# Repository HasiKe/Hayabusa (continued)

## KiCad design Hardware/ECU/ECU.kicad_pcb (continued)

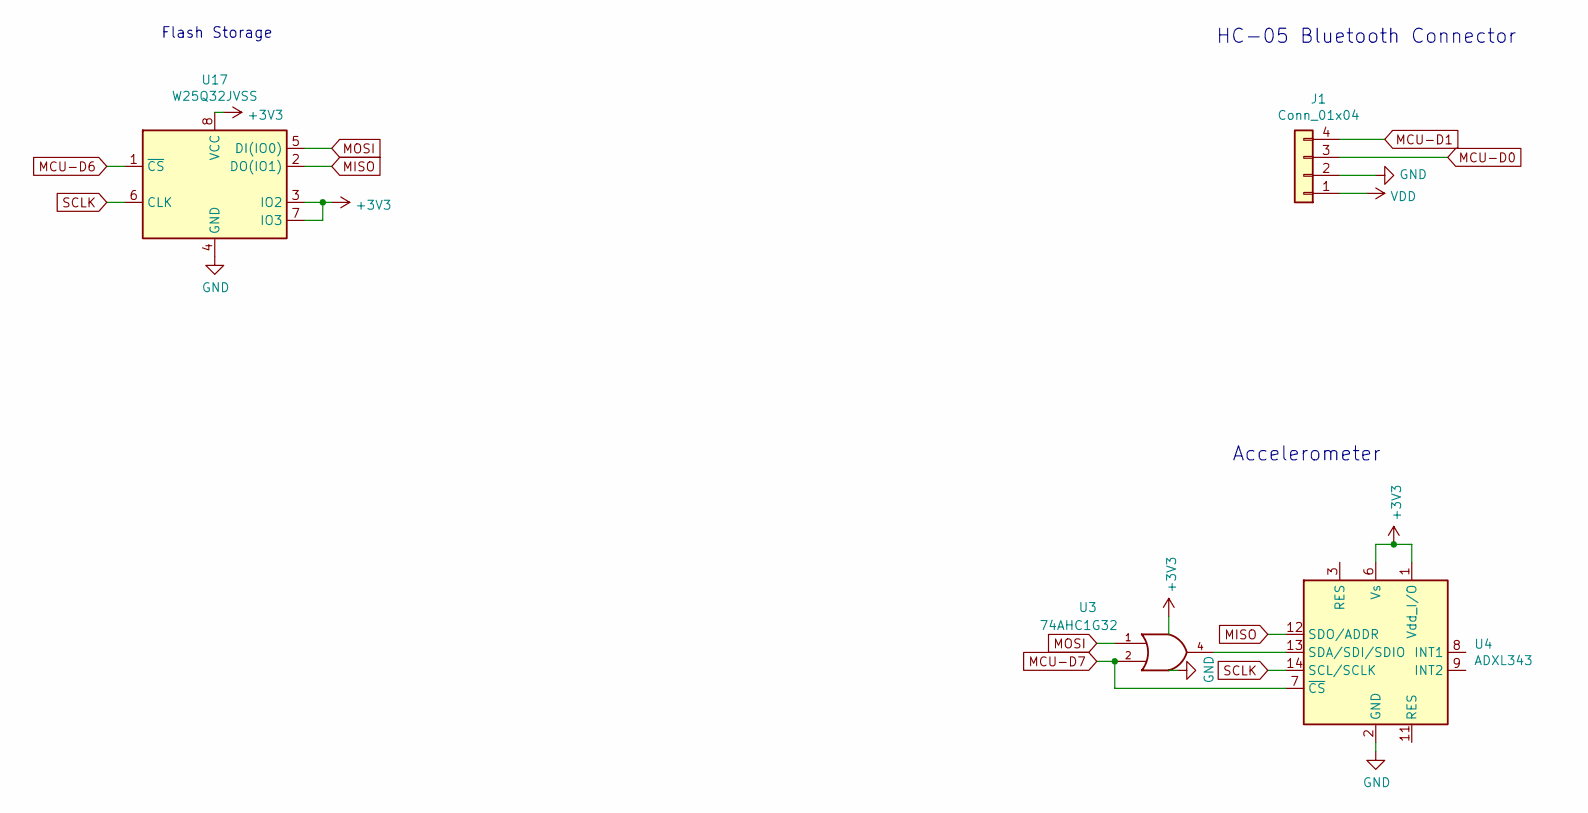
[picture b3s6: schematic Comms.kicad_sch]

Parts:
J1: Conn_01x04; PinHeader_1x04_P2.54mm_Vertical
U3: 74AHC1G32; SOT-353_SC-70-5; Manufacturer_Part_Number SN74AHC1G32DCKR; Digikey Part Number 296-8749-1-ND
U4: ADXL343; LGA-14_3x5mm_P0.8mm_LayoutBorder1x6y; Manufacturer_Part_Number ADXL343BCCZ-RL; Digikey Part Number ADXL343BCCZ-RLCT-ND
U17: W25Q32JVSS; SOIC-8_5.3x5.3mm_P1.27mm; Manufacturer_Part_Number W25Q32JVSSIQ; Digikey Part Number W25Q32JVSSIQCT-ND

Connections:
+3V3: U3.5 (VCC), U4.1 (Vdd_I/O), U4.6 (Vs), U17.3 (IO2), U17.7 (IO3), U17.8 (VCC); also elsewhere on the board
+5V: J1.1; also elsewhere on the board
GND: J1.2, U3.3 (GND), U4.2 (GND), U4.4 (GND), U4.5 (GND), U17.4 (GND); also elsewhere on the board
MCU-D0: J1.3; also elsewhere on the board
MCU-D1: J1.4; also elsewhere on the board
MCU-D6: U17.1 (~CS); also elsewhere on the board
MCU-D7: U3.2, U4.7 (~CS); also elsewhere on the board
MISO: U4.12 (SDO/ADDR), U17.2 (DO(IO1)); also elsewhere on the board
MOSI: U3.1, U17.5 (DI(IO0)); also elsewhere on the board
unnamed: U3.4, U4.13 (SDA/SDI/SDIO)
SCLK: U4.14 (SCL/SCLK), U17.6 (CLK); also elsewhere on the board

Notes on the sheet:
Flash Storage
HC-05 Bluetooth Connector
Accelerometer

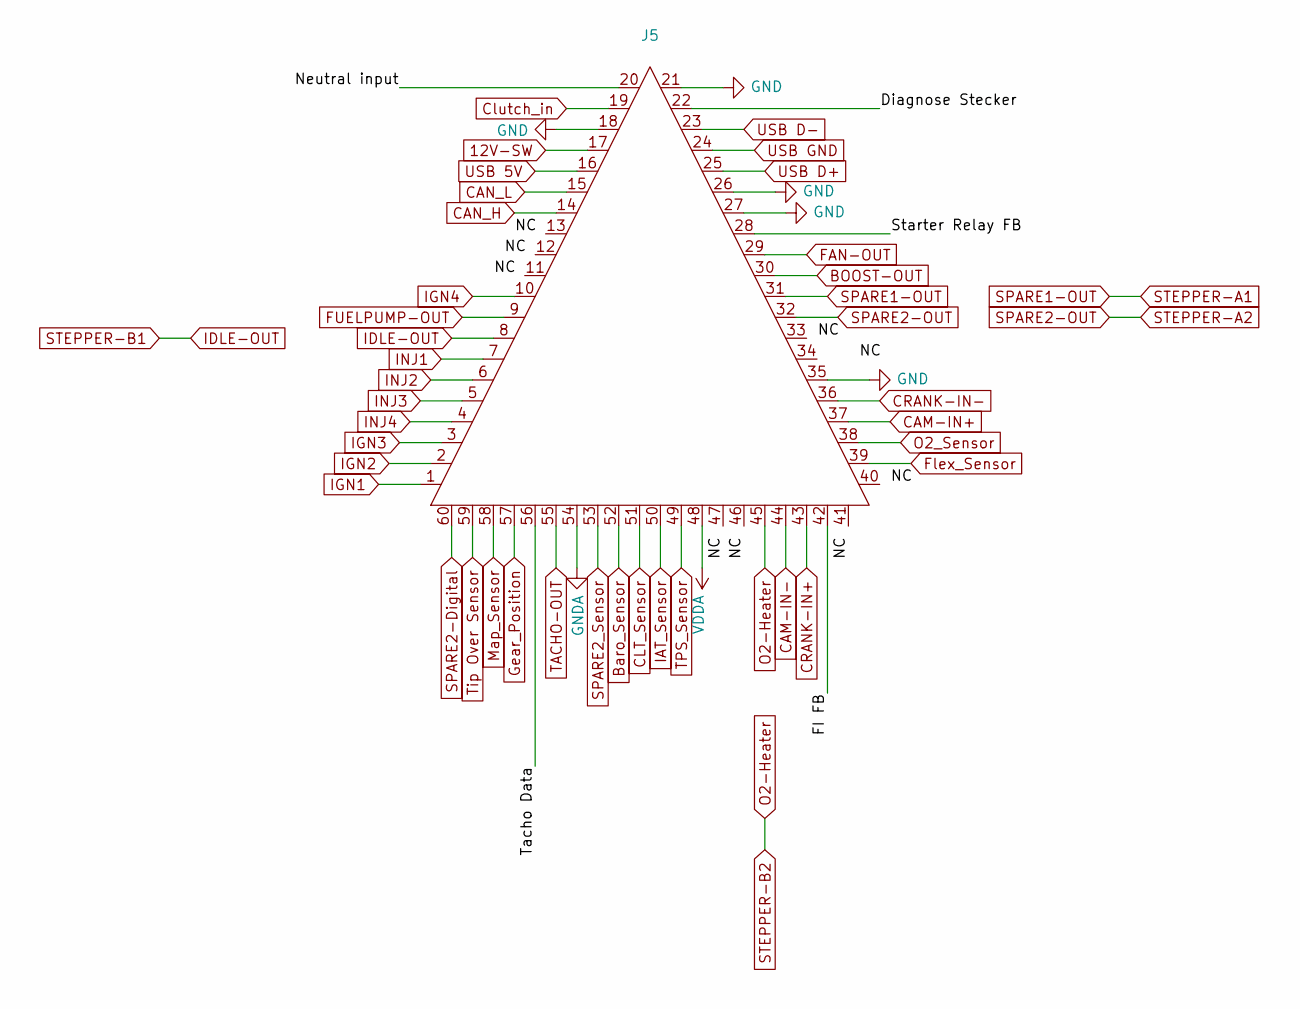
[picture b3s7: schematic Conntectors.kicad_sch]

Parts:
J5: 6437288-3

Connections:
12V-SW: J5.17; also elsewhere on the board
/Conntectors/Diagnose Stecker: J5.22
/Conntectors/FI FB: J5.42
/Conntectors/Neutral input: J5.20
/Conntectors/Starter Relay FB: J5.28
/Conntectors/Tacho Data: J5.56
ADC-Clamp-5: J5.39; also elsewhere on the board
BOOST-OUT: J5.30; also elsewhere on the board
Baro_Sensor: J5.52; also elsewhere on the board
CAM-IN+: J5.37; also elsewhere on the board
CAM-IN-: J5.44; also elsewhere on the board
CAN_H: J5.14
CAN_L: J5.15
CLT_Sensor: J5.51; also elsewhere on the board
CRANK-IN+: J5.43; also elsewhere on the board
CRANK-IN-: J5.36; also elsewhere on the board
Clutch_in: J5.19; also elsewhere on the board
FAN-OUT: J5.29; also elsewhere on the board
GND: J5.18, J5.21, J5.26, J5.27, J5.35; also elsewhere on the board
GNDA: J5.54; also elsewhere on the board
Gear_Position: J5.57; also elsewhere on the board
IAT_Sensor: J5.50; also elsewhere on the board
IDLE-OUT: J5.8; also elsewhere on the board
IGN1: J5.1; also elsewhere on the board
IGN2: J5.2; also elsewhere on the board
IGN3: J5.3; also elsewhere on the board
IGN4: J5.10; also elsewhere on the board
INJ1: J5.7; also elsewhere on the board
INJ2: J5.6; also elsewhere on the board
INJ3: J5.5; also elsewhere on the board
INJ4: J5.4; also elsewhere on the board
Map_Sensor: J5.58; also elsewhere on the board
O2-Heater: J5.45; also elsewhere on the board
O2_Sensor: J5.38; also elsewhere on the board
ROUT2: J5.55; also elsewhere on the board
SPARE1-OUT: J5.31; also elsewhere on the board
SPARE2-Digital: J5.60; also elsewhere on the board
SPARE2-OUT: J5.32; also elsewhere on the board
SPARE2_Sensor: J5.53; also elsewhere on the board
TPS_Sensor: J5.49; also elsewhere on the board
Tip Over Sensor: J5.59; also elsewhere on the board
USB 5V: J5.16; also elsewhere on the board
USB D+: J5.25; also elsewhere on the board
USB D-: J5.23; also elsewhere on the board
USB GND: J5.24; also elsewhere on the board
VDDA: J5.48; also elsewhere on the board

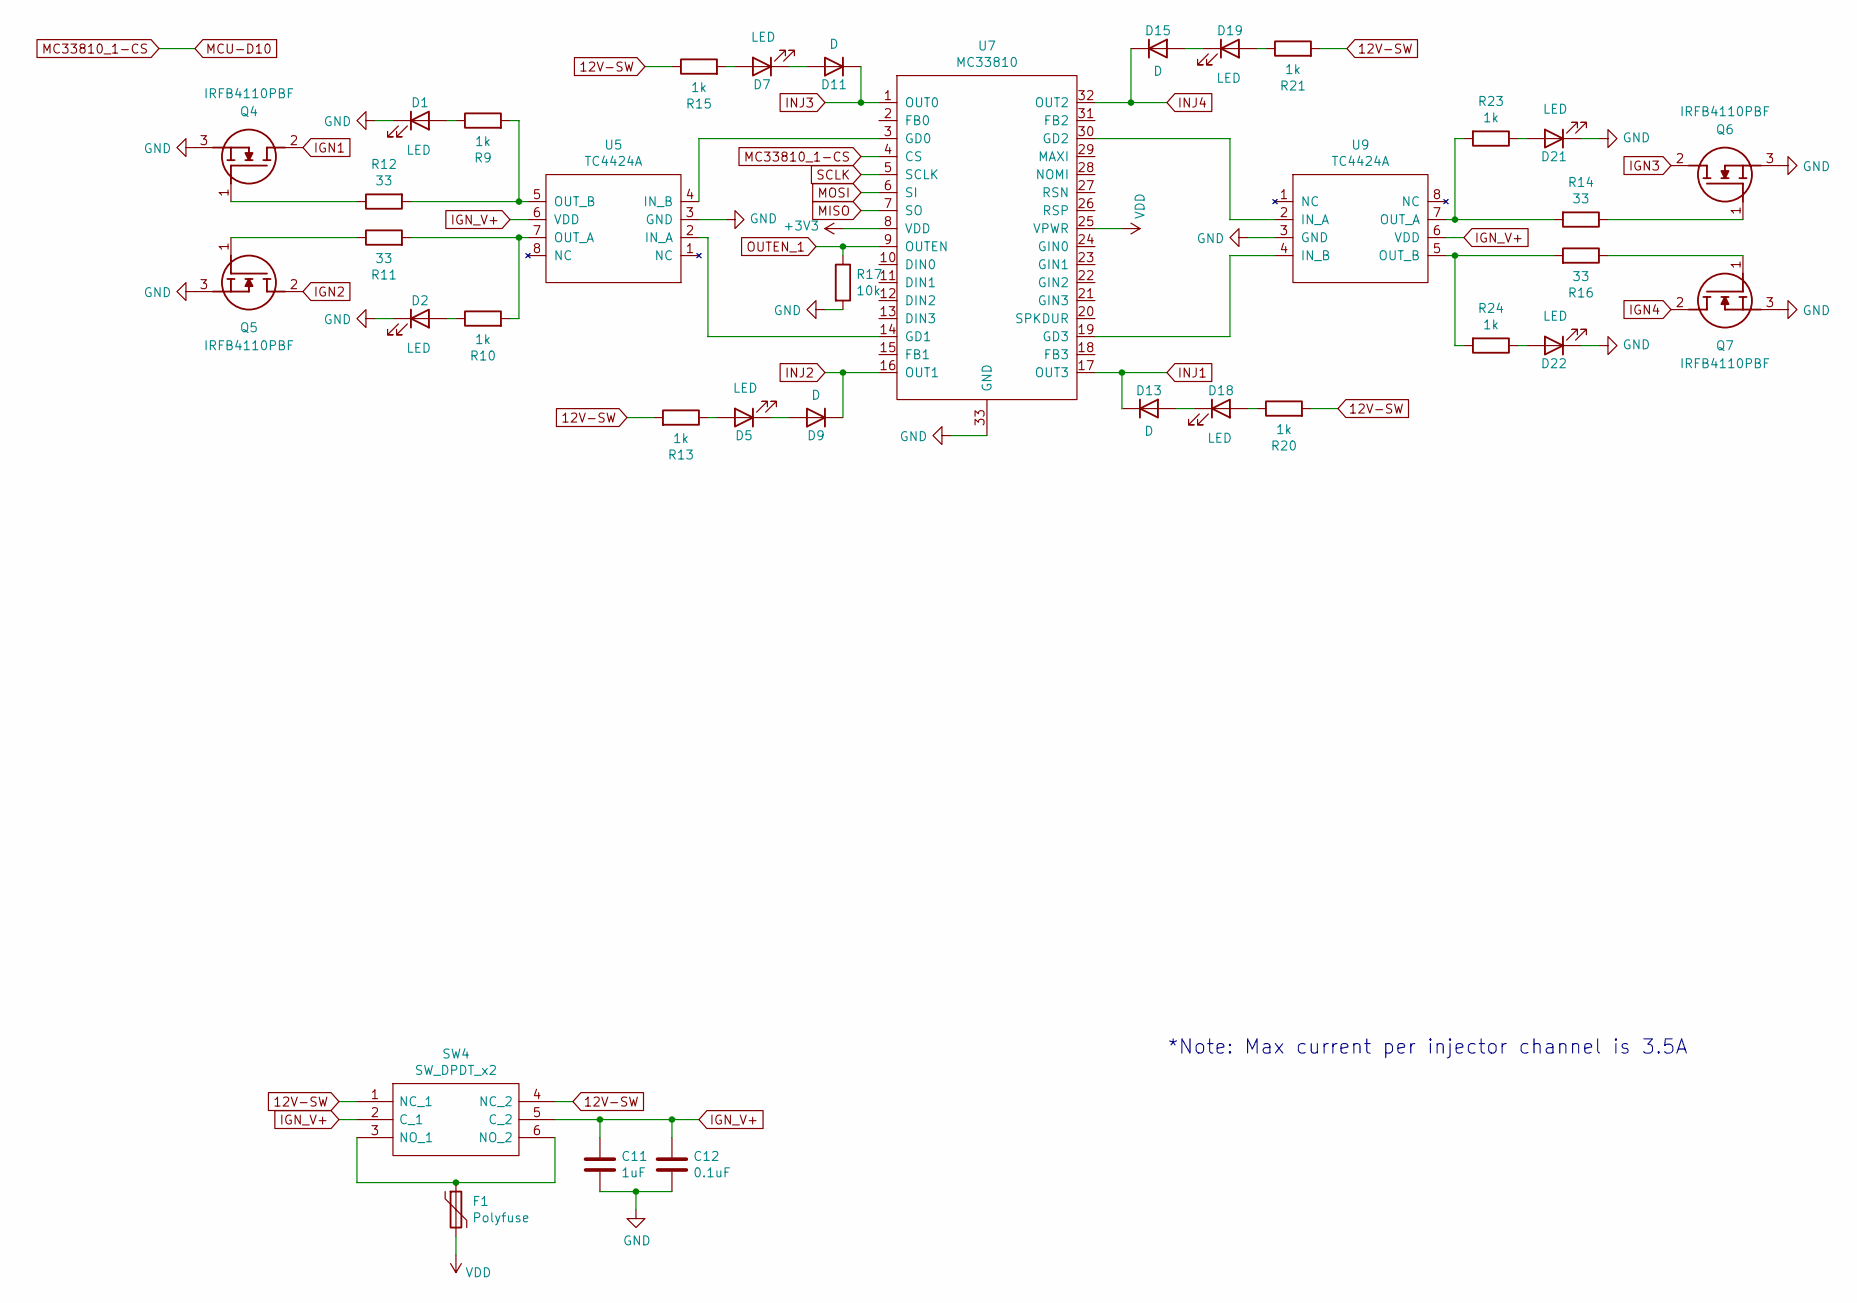
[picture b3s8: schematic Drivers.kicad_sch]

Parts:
C11: 1uF; C_0805_2012Metric; Manufacturer_Part_Number CC0805KKX7R7BB105; Digikey Part Number 311-1365-1-ND
C12: 0.1uF; C_0805_2012Metric; Manufacturer_Part_Number CC0805KRX7R9BB104; Digikey Part Number 311-1140-1-ND
D1, D2, D21, D22: LED; LED_0805_2012Metric; Manufacturer_Part_Number SML-H12D8TT86C; Digikey Part Number SML-H12D8TT86CCT-ND
D5, D7, D18, D19: LED; LED_0805_2012Metric; Manufacturer_Part_Number LH R974-LP-1; Digikey Part Number 475-1415-1-ND
D9, D11, D13, D15: D; D_SOD-323; Manufacturer_Part_Number 1N4448WX-TP; Digikey Part Number 1N4448WXTPMSCT-ND
F1: Polyfuse; Fuse_1812_4532Metric; Manufacturer_Part_Number 0ZCC0050FF2C; Digikey Part Number 507-1361-1-ND
Q4, Q5, Q6, Q7: IRFB4110PBF; TO254P483X1016X1994-3P; Mouser Part Number 942-IRFB4110PBF
R9, R10, R13, R15, R20, R21, R23, R24: 1k; R_0805_2012Metric; Manufacturer_Part_Number RC0805FR-071KL; Digikey Part Number 311-1.00KCRCT-ND
R11, R12, R14, R16: 33; R_0805_2012Metric; Manufacturer_Part_Number RC0805FR-7W33RL; Digikey Part Number RC0805FR-7W33RL
R17: 10k; R_0805_2012Metric; Manufacturer_Part_Number RC0805JR-0710KL; Digikey Part Number 311-10KARCT-ND
SW4: SW_DPDT_x2; AYZ0202AGRLC; Manufacturer_Part_Number AYZ0202AGRLC; Digikey Part Number 401-2013-1-ND
U5, U9: TC4424A; SOIC-8_3.9x4.9mm_P1.27mm; Manufacturer_Part_Number TC4424AVOA; Digikey Part Number TC4424AVOA-ND
U7: MC33810; SOIC32-P0.65-33N; Manufacturer_Part_Number MCZ33810EK

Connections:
12V-SW: R13.2, R15.1, R20.2, R21.2, SW4.1 (NC_1), SW4.4 (NC_2); also elsewhere on the board
+3V3: U7.8 (VDD); also elsewhere on the board
+5V: F1.2, U7.25 (VPWR); also elsewhere on the board
GND: C11.2, C12.2, D1.1 (K), D2.1 (K), D21.1 (K), D22.1 (K), Q4.3 (S), Q5.3 (S), Q6.3 (S), Q7.3 (S), R17.2, U5.3 (GND), U7.33 (GND), U9.3 (GND); also elsewhere on the board
IGN1: Q4.2 (D); also elsewhere on the board
IGN2: Q5.2 (D); also elsewhere on the board
IGN3: Q6.2 (D); also elsewhere on the board
IGN4: Q7.2 (D); also elsewhere on the board
IGN_V+: C11.1, C12.1, SW4.2 (C_1), SW4.5 (C_2), U5.6 (VDD), U9.6 (VDD)
INJ1: D13.1 (K), U7.17 (OUT3); also elsewhere on the board
INJ2: D9.1 (K), U7.16 (OUT1); also elsewhere on the board
INJ3: D11.1 (K), U7.1 (OUT0); also elsewhere on the board
INJ4: D15.1 (K), U7.32 (OUT2); also elsewhere on the board
MC33810_1-CS: U7.4 (CS); also elsewhere on the board
MISO: U7.7 (SO); also elsewhere on the board
MOSI: U7.6 (SI); also elsewhere on the board
unnamed: D1.2 (A), R9.1
unnamed: D2.2 (A), R10.1
unnamed: D5.2 (A), R13.1
unnamed: D5.1 (K), D9.2 (A)
unnamed: D7.2 (A), R15.2
unnamed: D7.1 (K), D11.2 (A)
unnamed: D13.2 (A), D18.1 (K)
unnamed: D15.2 (A), D19.1 (K)
unnamed: D18.2 (A), R20.1
unnamed: D19.2 (A), R21.1
unnamed: D21.2 (A), R23.1
unnamed: D22.2 (A), R24.1
unnamed: Q4.1 (G), R12.1
unnamed: Q5.1 (G), R11.1
unnamed: Q6.1 (G), R14.1
unnamed: Q7.1 (G), R16.1
unnamed: F1.1, SW4.3 (NO_1), SW4.6 (NO_2)
unnamed: U5.2 (IN_A), U7.14 (GD1)
unnamed: U5.4 (IN_B), U7.3 (GD0)
unnamed: R10.2, R11.2, U5.7 (OUT_A)
unnamed: R9.2, R12.2, U5.5 (OUT_B)
unnamed: U7.30 (GD2), U9.2 (IN_A)
unnamed: U7.19 (GD3), U9.4 (IN_B)
unnamed: R14.2, R23.2, U9.7 (OUT_A)
unnamed: R16.2, R24.2, U9.5 (OUT_B)
OUTEN_1: R17.1, U7.9 (OUTEN)
SCLK: U7.5 (SCLK); also elsewhere on the board

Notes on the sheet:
*Note: Max current per injector channel is 3.5A

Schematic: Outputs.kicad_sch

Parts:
A1: Pololu_Breakout_DRV8825; Pololu_Breakout-16_15.2x20.3mm
C31: 100uF; CP_Elec_6.3x7.7; Manufacturer_Part_Number EEE-FT1V101AV; Digikey Part Number P124821CT-ND
D25, D26, D28, D29, D30, D31: D; D_SOD-323; Manufacturer_Part_Number 1N4448WX-TP; Digikey Part Number 1N4448WXTPMSCT-ND
D27: D_Schottky; D_PowerDI-123; Manufacturer_Part_Number DFLS2100-7; Digikey Part Number DFLS2100-7DICT-ND
IC2, IC3, IC4: ZXMS6006DT8; SOT153P700X170-8N; Manufacturer_Part_Number ZXMS6006DT8; Digikey Part Number ZXMS6006DT8TADICT-ND
R53, R54, R58, R59, R60, R61: 1k; R_0805_2012Metric_Pad1.20x1.40mm_HandSolder; Manufacturer_Part_Number RC0805FR-071KL; Digikey Part Number 311-1.00KCRCT-ND
R55, R56, R62, R63, R64, R65: 100k; R_0805_2012Metric_Pad1.20x1.40mm_HandSolder; Manufacturer_Part_Number RC0805FR-07100KL; Digikey Part Number 311-100KCRCT-ND
R57: 10k; R_0805_2012Metric; Manufacturer_Part_Number RC0805JR-0710KL; Digikey Part Number 311-10KARCT-ND

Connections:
12V-SW: D25.1 (K), D26.1 (K), D27.2 (A), D28.1 (K), D29.1 (K), D30.1 (K), D31.1 (K), R57.2; also elsewhere on the board
+3V3: A1.13 (~RST), A1.14 (~SLP); also elsewhere on the board
BOOST-OUT: D29.2 (A), IC4.5 (DRAIN_2_1), IC4.6 (DRAIN_2_2); also elsewhere on the board
FAN-OUT: D28.2 (A), IC4.7 (DRAIN_1_1), IC4.8 (DRAIN_1_2); also elsewhere on the board
GND: A1.1 (GND), A1.7 (GND), C31.2, IC2.2 (SOURCE_1), IC2.4 (SOURCE_2), IC3.2 (SOURCE_1), IC3.4 (SOURCE_2), IC4.2 (SOURCE_1), IC4.4 (SOURCE_2), R55.1, R56.1, R62.2, R63.1, R64.2, R65.1; also elsewhere on the board
IDLE-OUT: A1.5 (B1), D25.2 (A), IC2.7 (DRAIN_1_1), IC2.8 (DRAIN_1_2); also elsewhere on the board
MCU-D24: R61.2; also elsewhere on the board
MCU-D25: R60.2; also elsewhere on the board
MCU-D26: R54.2; also elsewhere on the board
MCU-D27: R53.2; also elsewhere on the board
MCU-D28: R59.2; also elsewhere on the board
MCU-D29: R58.2; also elsewhere on the board
MCU-D30: A1.9 (~EN); also elsewhere on the board
MCU-D31: A1.15 (STEP); also elsewhere on the board
MCU-D32: A1.16 (DIR); also elsewhere on the board
unnamed: A1.8 (VMOT), C31.1, D27.1 (K)
unnamed: IC2.1 (INPUT_1), R53.1, R55.2
unnamed: IC2.3 (INPUT_2), R54.1, R56.2
unnamed: IC3.1 (INPUT_1), R58.1, R62.1
unnamed: IC3.3 (INPUT_2), R59.1, R63.2
unnamed: IC4.1 (INPUT_1), R60.1, R64.1
unnamed: IC4.3 (INPUT_2), R61.1, R65.2
O2-Heater: A1.6 (B2); also elsewhere on the board
ROUT2: R57.1; also elsewhere on the board
SPARE1-OUT: A1.4 (A1), D30.2 (A), IC3.7 (DRAIN_1_1), IC3.8 (DRAIN_1_2); also elsewhere on the board
SPARE2-OUT: A1.3 (A2), D26.2 (A), IC2.5 (DRAIN_2_1), IC2.6 (DRAIN_2_2); also elsewhere on the board
SPARE2_OUT: D31.2 (A), IC3.5 (DRAIN_2_1), IC3.6 (DRAIN_2_2)

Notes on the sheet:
VVT and Spare 1
Stepper Driver (DRV8825)
Tacho output
PWM Idle and Spare 2 outputs
Fan and Boost outputs
Fuel pump relay

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
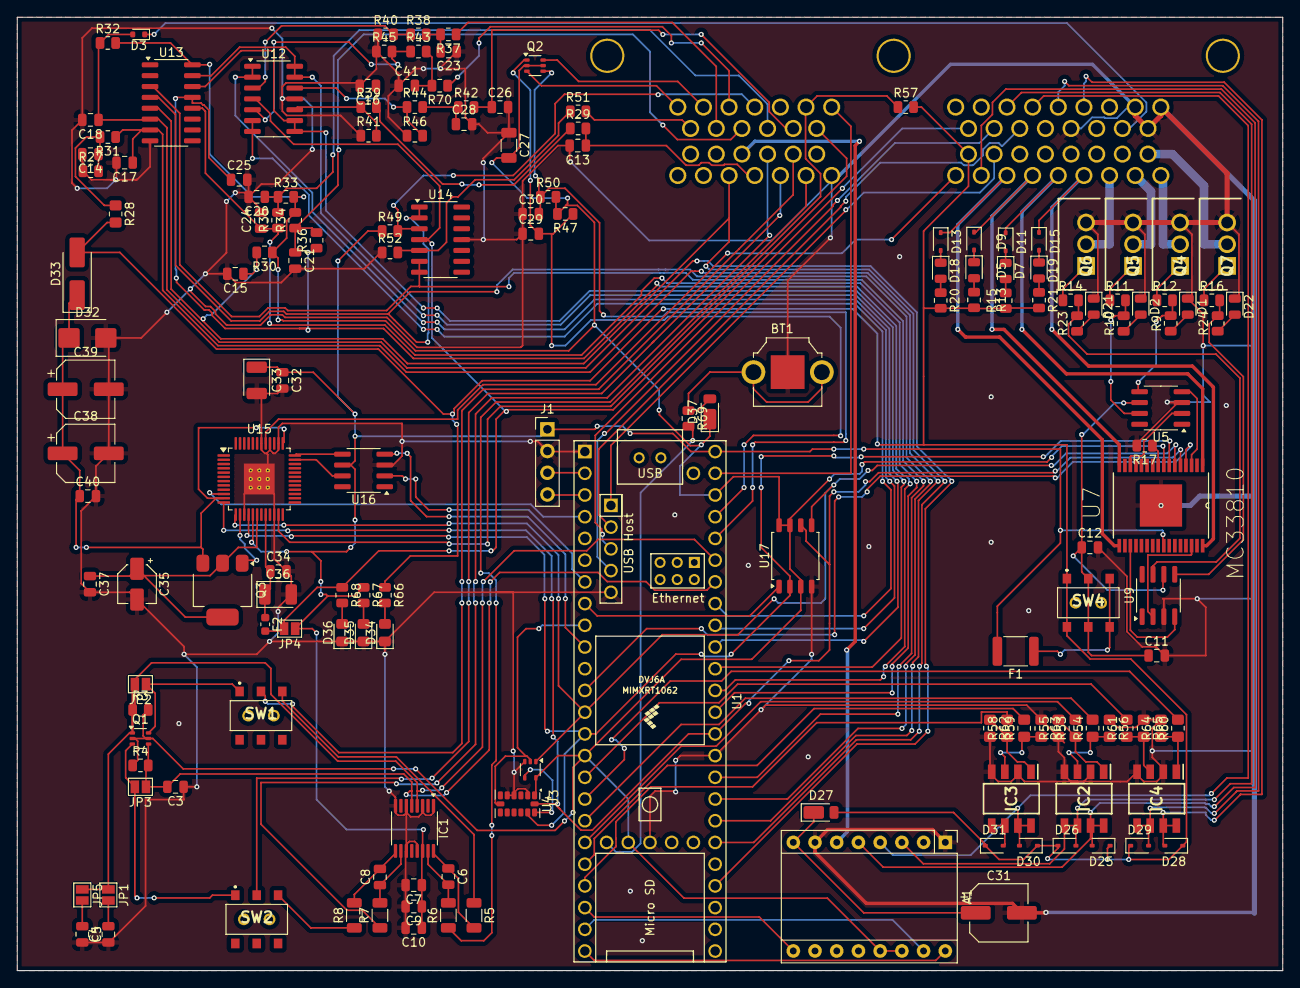
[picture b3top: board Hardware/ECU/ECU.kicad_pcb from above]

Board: 2 copper layers, 148.0 x 111.5 mm, 162 parts (0 on the bottom side), 145 nets.

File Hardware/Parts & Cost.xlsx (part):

Item | Qty | Reference(s) | Value | LibPart | Footprint | Datasheet | DNP | Allied_Number | Arrow Part Number | Arrow Price/Stock | Datasheet | Description | Digikey Part Number | Footprint | Height | Manufacturer_Name | Manufacturer_Part_Number | Mouser Part Number | Mouser Price/Stock | RS Part Number | RS Price/Stock | Sim.Device | Sim.Library | Sim.Pins | Tolerance | URL | Voltage
1 | 1 | A1 | Pololu_Breakout_DRV8825 | Driver_Motor:Pololu_Breakout_DRV8825 | Module:Pololu_Breakout-16_15.2x20.3mm | https://www.pololu.com/product/2982 |  |  |  |  | https://www.pololu.com/product/2982 | Pololu Breakout Board, Stepper Driver DRV8825 |  | Module:Pololu_Breakout-16_15.2x20.3mm
2 | 1 | BT1 | Battery_Cell | Device:Battery_Cell | 2999:BAT_2999 | ~ |  |  |  |  | ~ | Single-cell battery | 36-2999-ND | 2999:BAT_2999 |  | Keystone | 2999 |  |  |  |  |  |  |  |  | https://www.digikey.com.au/product-detail/en/keystone-electr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
3 | 14 | C3, C9, C12, C13, C14, C20, C21, C23, C26, C32, C34, C37, C40, C41 | 0.1uF | Device:C | Capacitor_SMD:C_0805_2012Metric | ~ |  |  |  |  | ~ | Unpolarized capacitor | 311-1140-1-ND | Capacitor_SMD:C_0805_2012Metric |  | Yageo | CC0805KRX7R9BB104 |  |  |  |  |  |  |  |  | https://www.digikey.com.au/product-detail/en/yageo/CC0805KRX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
4 | 4 | C4, C7, C29, C30 | 0.01uF | Device:C | Capacitor_SMD:C_0805_2012Metric | ~ |  |  |  |  | ~ | Unpolarized capacitor | 311-1136-1-ND | Capacitor_SMD:C_0805_2012Metric |  | Yageo | CC0805KRX7R9BB103 |  |  |  |  |  |  |  |  | https://www.digikey.com/product-detail/en/yageo/CC0805KRX7R9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
5 | 1 | C5 | 4700pF | Device:C | Capacitor_SMD:C_0805_2012Metric | ~ |  |  |  |  | ~ | Unpolarized capacitor | 311-1133-1-ND | Capacitor_SMD:C_0805_2012Metric |  | Yageo | CC0805KRX7R9BB472 |  |  |  |  |  |  |  |  | https://www.digikey.com/product-detail/en/yageo/CC0805KRX7R9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
6 | 2 | C6, C8 | 1nF | Device:C | Capacitor_SMD:C_0805_2012Metric | ~ |  |  |  |  | ~ | Unpolarized capacitor | 399-16591-1-ND | Capacitor_SMD:C_0805_2012Metric |  | Kemet | C0805C102J5HACAUTO |  |  |  |  |  |  |  |  | https://www.digikey.com/product-detail/en/kemet/C0805C102J5H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
7 | 2 | C10, C11 | 1uF | Device:C | Capacitor_SMD:C_0805_2012Metric | ~ |  |  |  |  | ~ | Unpolarized capacitor | 311-1365-1-ND | Capacitor_SMD:C_0805_2012Metric |  | Yageo | CC0805KKX7R7BB105 |  |  |  |  |  |  |  |  | https://www.digikey.com/product-detail/en/yageo/CC0805KKX7R7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
8 | 2 | C15, C18 | 270nF | Device:C | Capacitor_SMD:C_0805_2012Metric | ~ |  |  |  |  | ~ | Unpolarized capacitor | 311-4268-1-ND | Capacitor_SMD:C_0805_2012Metric |  | Yageo | CC0805JRX7R7BB274 |  |  |  |  |  |  |  |  | https://www.digikey.com.au/product-detail/en/yageo/CC0805JRX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
9 | 5 | C16, C17, C24, C25, C28 | 0.22uF | Device:C | Capacitor_SMD:C_0805_2012Metric | ~ |  |  |  |  | ~ | Unpolarized capacitor | 1276-1284-1-ND | Capacitor_SMD:C_0805_2012Metric |  | Samsung | CL21B224KOCNNNC |  |  |  |  |  |  |  |  | https://www.digikey.com/product-detail/en/samsung-electro-me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
10 | 1 | C27 | 100uF | Device:C | Capacitor_SMD:C_1206_3216Metric | ~ |  |  |  |  | ~ | Unpolarized capacitor | 1276-1782-1-ND | Capacitor_SMD:C_1206_3216Metric |  | Samsung | CL31A107MQHNNNE |  |  |  |  |  |  |  |  | https://www.digikey.com.au/product-detail/en/samsung-electro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
11 | 1 | C31 | 100uF | Device:CP | Capacitor_SMD:CP_Elec_6.3x7.7 |  |  |  |  |  |  |  | P124821CT-ND | Capacitor_SMD:CP_Elec_6.3x7.7 |  | Panasonic | EEE-FT1V101AV |  |  |  |  |  |  |  |  | https://www.digikey.com.au/product-detail/en/panasonic-elect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
12 | 2 | C33, C36 | 47uF | Device:CP | Capacitor_Tantalum_SMD:CP_EIA-3528-21_Kemet-B |  |  |  |  |  |  |  | 478-1692-1-ND | Capacitor_Tantalum_SMD:CP_EIA-3528-21_Kemet-B |  | AVX | TAJB476K006RNJ |  |  |  |  |  |  |  |  | https://www.digikey.com/product-detail/en/avx-corporation/TA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 | 10V
13 | 1 | C35 | 22uF | Device:CP | Capacitor_SMD:CP_Elec_4x5.4 |  |  |  |  |  |  |  | EEE-1CA220WR | Capacitor_SMD:CP_Elec_4x5.4 |  | Panasonic | PCE3882CT-ND |  |  |  |  |  |  |  |  | https://www.digikey.com.au/product-detail/en/panasonic-elect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 | 10v
14 | 2 | C38, C39 | 33uF | Device:CP | Capacitor_SMD:CP_Elec_6.3x7.7 |  |  |  |  |  |  |  | PCE3925CT-ND | Capacitor_SMD:CP_Elec_6.3x7.7 |  | Panasonic | EEE-1HA330XP |  |  |  |  |  |  |  |  | https://www.digikey.com.au/product-detail/en/panasonic-elect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 | 50V
15 | 8 | D1, D2, D5, D7, D18, D19, D21, D22 | LED | Device:LED | LED_SMD:LED_0805_2012Metric | ~ |  |  |  |  | ~ | Light emitting diode | SML-H12D8TT86CCT-ND | LED_SMD:LED_0805_2012Metric |  | Rohm Semiconductor | SML-H12D8TT86C |  |  |  |  |  |  |  |  | https://www.digikey.com.au/product-detail/en/rohm-semiconduc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
16 | 1 | D3 | 1N4148WT | Diode:1N4148WT | Diode_SMD:D_SOD-523 | https://www.diodes.com/assets/Datasheets/ds30396.pdf |  |  |  |  | https://www.diodes.com/assets/Datasheets/ds30396.pdf | 75V 0.15A Fast switching Diode, SOD-523 |  | Diode_SMD:D_SOD-523 |  |  |  |  |  |  |  | D |  | 1=K 2=A
17 | 10 | D9, D11, D13, D15, D25, D26, D28, D29, D30, D31 | D | Device:D | Diode_SMD:D_SOD-323 | ~ |  |  |  |  | ~ | Diode | 1N4448WXTPMSCT-ND | Diode_SMD:D_SOD-323 |  | MCC | 1N4448WX-TP |  |  |  |  |  |  |  |  | https://www.digikey.com/product-detail/en/micro-commercial-c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
18 | 2 | D27, D37 | D_Schottky | Device:D_Schottky | Diode_SMD:D_PowerDI-123 | ~ |  |  |  |  | ~ | Schottky diode | DFLS2100-7DICT-ND | Diode_SMD:D_PowerDI-123 |  | Diodes Inc. | DFLS2100-7 |  |  |  |  |  |  |  |  | https://www.digikey.com/product-detail/en/diodes-incorporate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
19 | 1 | D32 | D_TVS | Device:D_Zener | Diode_SMD:D_SMB | ~ |  |  |  |  | ~ | Zener diode | SMBJ40A-QCT-ND | Diode_SMD:D_SMB |  | Bournes Inc. | SMBJ40A-Q |  |  |  |  |  |  |  |  | https://www.digikey.com.au/product-detail/en/bourns-inc/SMBJ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
20 | 1 | D33 | D_Schottky | Device:D_Schottky | Diode_SMD:D_SMA_Handsoldering | ~ |  |  |  |  | ~ | Schottky diode | B360A-FDICT-ND | Diode_SMD:D_SMA_Handsoldering |  | Diodes Inc | B360A-13-F |  |  |  |  |  |  |  |  | https://www.digikey.com.au/product-detail/en/diodes-incorpor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
21 | 3 | D34, D35, D36 | LED | Device:LED | LED_SMD:LED_0805_2012Metric_Pad1.15x1.40mm_HandSolder | ~ |  |  |  |  | ~ | Light emitting diode | 475-1410-2-ND | LED_SMD:LED_0805_2012Metric_Pad1.15x1.40mm_HandSolder |  | OSRAM | LG R971-KN-1 |  |  |  |  |  |  |  |  | https://www.digikey.com/en/products/detail/osram-opto-semico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
22 | 1 | F1 | Polyfuse | Device:Polyfuse | Fuse:Fuse_1812_4532Metric | ~ |  |  |  |  | ~ | Resettable fuse, polymeric positive temperature coefficient | 507-1361-1-ND | Fuse:Fuse_1812_4532Metric |  | Bel Fuse Inc. | 0ZCC0050FF2C |  |  |  |  |  |  |  |  | https://www.digikey.com.au/product-detail/en/bel-fuse-inc/0Z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
23 | 1 | F2 | Polyfuse | Device:Fuse | Fuse:Fuse_0603_1608Metric | ~ |  |  |  |  | ~ | Fuse | 507-1817-1-ND | Fuse:Fuse_0603_1608Metric |  | Bel Fuse Inc. | 0ZCM0008FF2G |  |  |  |  |  |  |  |  | https://www.digikey.com.au/product-detail/en/bel-fuse-inc/0Z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
24 | 1 | IC1 | MAX9926UAEE_V+ | IC_Automotive:MAX9926UAEE_V+ | Package_SO:QSOP-16_3.9x4.9mm_P0.635mm | https://componentsearchengine.com/Datasheets/1/MAX9926UAEE_V+.pdf |  |  |  |  | https://componentsearchengine.com/Datasheets/1/MAX9926UAEE_V+.pdf | Sensor Interface Variable-Reluctance Sensor Interface | MAX9926UAEE/V+-ND | Package_SO:QSOP-16_3.9x4.9mm_P0.635mm | 27395 | Maxim Integrated | MAX9926UAEE/V+ | 700-MAX9926UAEE/V+ | https://www.mouser.com/Search/Refine.aspx?Keyword=700-MAX992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 |  |  |  |  |  |  | https://www.digikey.com.au/product-detail/en/maxim-integrate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
25 | 3 | IC2, IC3, IC4 | ZXMS6006DT8 | IC_Automotive:ZXMS6006DT8 | ZXMS6006DT8TA:SOT153P700X170-8N |  |  |  |  |  |  | Diodes Inc dual self protected low side MOSFET | ZXMS6006DT8TADICT-ND | ZXMS6006DT8TA:SOT153P700X170-8N | 27395 | Diodes Inc | ZXMS6006DT8 |  |  |  |  |  |  |  |  | https://www.digikey.com.au/en/products/detail/diodes-incorpo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

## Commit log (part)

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2024-11-06 init
2024-11-06 push up to date
2024-11-06 new file: .gitmodules new file: speeduino modified: Hardware/ECU/ECU.kicad_sch deleted: Hardware/ECU/~ECU.kicad_sch.lck Hardware/ECU/ECU-backups/ECU-2024-11-06_132318.zip Hardware/ECU/ECU-backups/ECU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
2024-11-06 new file: Hardware/ECU/ECU-backups/ECU-2024-11-06_180755.zip new file: Hardware/ECU/ECU-backups/ECU-2024-11-06_185548.zip new file: Hardware/ECU/ECU-backups/ECU-2024-11-06_190414.zip new file: Hardwa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
2024-11-07 Hardware/ECU/lib/2999/ Hardware/ECU/lib/IC_Automotive/IC_Automotive.pretty/BAT_2999.kicad_mod Hardware/ECU/lib/IC_Automotive/IC_Automotive.pretty/ZXMS6006DT8TA.kicad_mod Hardware/ECU/lib/ZXMS6006DT8T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
2024-11-07 modified: Hardware/ECU/fp-lib-table Hardware/ECU/ECU-backups/ECU-2024-11-08_000501.zip Hardware/ECU/lib/teensy.pretty/
2024-11-07 new file: Hardware/ECU/ECU-backups/ECU-2024-11-08_000501.zip new file: Hardware/ECU/lib/teensy.pretty new file: tune/Hayabusa-R1/CurrentTune.msq new file: tune/Hayabusa-R1/DataLogs/SPD_0001.csv new f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
2024-11-08 modified: .gitmodules modified: Hardware/ECU/Comms.kicad_sch modified: Hardware/ECU/ECU.kicad_pcb modified: Hardware/ECU/ECU.kicad_pro modified: Hardware/ECU/ECU.kicad_sch modified: Hardware/ECU/Inpu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
2024-12-18 Entferne Zone.Identifier-Dateien und füge neue Dokumente und Bibliotheken hinzu
2024-12-18 Aktualisiere Subprojekt-Commit und füge neue Bibliotheken sowie Anpassungen in der ECU-Konfiguration hinzu
2025-01-03 modified: Hardware/ECU/Conntectors.kicad_sch deleted: Hardware/ECU/ECU-backups/ECU-2024-10-31_195121.zip deleted: Hardware/ECU/ECU-backups/ECU-2024-10-31_200337.zip deleted: Hardware/ECU/ECU-backups/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
2025-01-06 new file: Hardware/ECU/ECU-backups/ECU-2024-12-18_220608.zip new file: Hardware/ECU/ECU-backups/ECU-2024-12-30_215431.zip new file: Hardware/ECU/ECU-backups/ECU-2024-12-31_001349.zip new file: Hardwa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
2025-05-08 update to Kicad v9
2025-05-11 PCB
    Platine Vernetzt
2025-05-13 PCB V0.1
    Erste Iteration der PCB vernetzt
2025-05-15 Add new footprint for TO-220AB MOSFET (IRFB4110PBF)
    - Created a new KiCad module for the TO254P483X1016X1994-3P footprint.
    - Included necessary graphical elements such as courtyard, fabrication, and silkscreen layers.
    - Defined pads for through-hole connections with appropriate dimensions and drill sizes.
    - Added a 3D model reference for the IRFB4110PBF component.
2025-05-18 PCB v0.2
    leiterbahndicke updated
    Clutch input rework
2025-05-19 modified: Hardware/ECU/Conntectors.kicad_sch deleted: Hardware/ECU/ECU-backups/ECU-2025-05-14_000421.zip deleted: Hardware/ECU/ECU-backups/ECU-2025-05-14_001426.zip deleted: Hardware/ECU/ECU-backups/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
2025-05-19 new file: Hardware/ECU/ECU-backups/ECU-2025-05-19_135220.zip new file: Hardware/ECU/ECU-backups/ECU-2025-05-19_140656.zip new file: Hardware/ECU/ECU-backups/ECU-2025-05-19_142320.zip new file: Hardwa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
2025-05-19 Update 5V Supply
    added TPS54202
2025-05-27 modified: Hardware/ECU/Drivers.kicad_sch deleted: Hardware/ECU/ECU-backups/ECU-2025-05-15_143348.zip deleted: Hardware/ECU/ECU-backups/ECU-2025-05-15_144355.zip deleted: Hardware/ECU/ECU-backups/ECU-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
2025-05-27 new file: Hardware/Parts & Cost.ods deleted: Hardware/Parts & Cost.xlsx
2025-05-27 modified: Hardware/Parts & Cost.ods
2025-05-27 PCB v0.3
    Ready to Build
2025-05-27 renamed: Hardware/ECU/ECU-backups/ECU-2025-05-27_141528.zip -> Hardware/ECU/ECU-backups/ECU-2025-05-27_234640.zip renamed: Hardware/ECU/ECU-backups/ECU-2025-05-27_154948.zip -> Hardware/ECU/ECU-backu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
2025-05-28 deleted: Hardware/ECU/ECU-backups/ECU-2025-05-17_000435.zip deleted: Hardware/ECU/ECU-backups/ECU-2025-05-17_001057.zip deleted: Hardware/ECU/ECU-backups/ECU-2025-05-17_001712.zip new file: Hardware/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
2025-06-15 Update Parts & Cost
    Update Parts & Cost
    add breaks, breakpump, disk etc.
    add fule pump, filter, pressure regulator
2025-06-25 deleted: Hardware/ECU/ECU-backups/ECU-2025-05-17_134922.zip deleted: Hardware/ECU/ECU-backups/ECU-2025-05-18_153853.zip deleted: Hardware/ECU/ECU-backups/ECU-2025-05-18_155339.zip deleted: Hardware/E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
2025-07-18 renamed: Hardware/ECU/ECU-backups/ECU-2025-05-20_142748.zip -> Hardware/ECU/ECU-backups/ECU-2025-06-26_114759.zip modified: Hardware/ECU/ECU.kicad_prl new file: "T\303\234V/10090018_ Philips_Ultinon_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
2025-07-21 Added Tire release
    Metzler Roadtec M9
2025-07-25 new file: "T\303\234V/Metzler Reifen.pdf"
2025-07-25 deleted: "T\303\234V/Metzler Reifen.pdf"
2025-08-08 deleted: Hardware/ECU/ECU-backups/ECU-2025-05-20_150003.zip deleted: Hardware/ECU/ECU-backups/ECU-2025-05-27_155558.zip deleted: Hardware/ECU/ECU-backups/ECU-2025-05-27_174943.zip new file: Hardware/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
2025-08-25 modified: Hardware/ECU/Drivers.kicad_sch deleted: Hardware/ECU/ECU-backups/ECU-2025-05-27_180718.zip new file: Hardware/ECU/ECU-backups/ECU-2025-08-25_112034.zip
2025-08-25 deleted: Hardware/ECU/ECU-backups/ECU-2025-05-27_234640.zip new file: Hardware/ECU/ECU-backups/ECU-2025-08-25_142135.zip
2025-10-01 new file: Hardware/Abgasstopfen/Abgas-Stopfen v1.step new file: Hardware/Abgasstopfen/Skizze.dxf new file: Hardware/Abgasstopfen/Skizze.png deleted: Hardware/ECU/ECU-backups/ECU-2025-05-28_135321.zip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
2025-12-19 new file: Hardware/Airbox/FB[1]-00-00.jpg new file: Hardware/Airbox/FB[1]-00-00.zip new file: Hardware/Airbox/IMG_4321.JPG new file: Hardware/Airbox/IMG_4328.JPG new file: Hardware/Airbox/airbox.stp 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
2025-12-19 new file: CHANGELOG.md modified: README.md new file: docs/HARDWARE.md new file: docs/INSTALLATION.md new file: docs/PROJECT_STRUCTURE.md new file: docs/SOFTWARE.md new file: docs/TUNING.md modified: 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
2026-01-19 deleted: Hardware/ECU/ECU-backups/ECU-2025-05-27_235240.zip deleted: Hardware/ECU/ECU-backups/ECU-2025-05-28_135321.zip deleted: Hardware/ECU/ECU-backups/ECU-2025-05-28_140049.zip deleted: Hardware/E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
2026-01-19 Füge .gitignore hinzu und ändere Dateiberechtigungen für mehrere Dateien
2026-01-20 Aktualisiere Subprojekt-Commit für Speeduino
2026-01-20 Fix speeduino submodule reference (remove invalid commit)
2026-01-27 added pinout sheet
2026-04-28 Restructure: move Hardware/ to hardware/, add new components and tunes
2026-04-30 Replace speeduino submodule with HasiKe fork, fix teensy.pretty path
    - Switch speeduino from speeduino/speeduino to HasiKe/speeduino
    - Fix teensy.pretty submodule path case mismatch (Hardware -> hardware)
    - Add ISL9V5036P3-F085 component library
    - Various ECU schematic updates
2026-04-30 Dokumentation überarbeitet: professioneller, Dropbear v2, Klopfsensor
    - Alle Dokumente auf Deutsch vereinheitlicht
    - Emojis reduziert (nur Status-Checkmarks)
    - Arduino Mega 2560 durch Dropbear v2 / Teensy 4.1 ersetzt
    - Klopfsensor als geplantes Feature dokumentiert
    - TUNING.md: Erfundene Werte entfernt, nur allgemeine Prinzipien
    - HasiKe Speeduino Fork referenziert
2026-04-30 new file: "T\303\234V/Brembo_ABE_Bremsscheibe_Vorne_Schwimmend.pdf" renamed: hardware/Nockenwellen einstellen/Hayabusa Standarn Nochenwellen einstellen.md -> docs/Hayabusa Standarn Nochenwellen einst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
2026-05-04 software update
2026-05-05 Hardware update V1.2
2026-05-05 explosionszeichnungen hinzugefügt
2026-05-07 added troque specs to docs
2026-05-07 added LC calc
